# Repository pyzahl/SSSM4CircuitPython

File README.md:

# SSSM4CircuitPython
Solar Scintillation Seeing Monitor (SSSM) for CircuitPython

A renewed verion of a SSSM for CircuitPython on a ESP32-S2 or -S3-TFT.

Project based on hardware described here
https://www.blackwaterskies.co.uk/2017/06/diy-solar-scintillation-seeing-monitor-sssm/
or originally here:
https://vdocuments.mx/an-inexpensive-solar-scintillation-seeing-monitor-circuit-an-inexpensive.html

Let me copy the intro to SSSM:

A guide to building an inexpensive Solar Scintillation Seeing Monitor. The SSSM is a handy device which monitors the atmospheric seeing conditions during solar imaging. This SSSM can be built for a fraction of the cost of commercially available devices. You can use the SSSM to monitor seeing conditions through the day, or even to control your camera to capture images during the best seeing conditions.

Background:
The original design for the SSSM was published by E. J. Seykora at the Department of Physics, East Carolina University.

Read also how to integrate with Firecapture:
http://www.firecapture.de/
http://www.joachim-stehle.de/downloads/SSSMon/SSSMonPluginManual.pdf

Adapted schematics, connected to A0 and A1 for the ESP32-S2/S3-TFT replacing the originally used arduino.

This project is based on CircuitPython Version 8 (all required Libs included for reference) running on a Adafruit ESP32-S2/S3-TFT. The S3 is faster and better suited.

Anyhwo, the new S3 seams to have issues with WiFi. WiFi is not required here in USB-Serial mode compatible with the original Firecapture SSSM plugin and interface. Anyways planns are to use for MQTT for web based publishing, this works with the ESP32-S2-TFT, even not long term stable. Causes "Wifi-OFF" Progra mhold on the S3. TDB. May be next gen/version of Circuit Python fixes it. 

Currently: CircuitPython 8.0.0-beta.6

https://circuitpython.org/board/adafruit_feather_esp32s3_tft/

Adafruit ESP32-S3 TFT Feather - 4MB Flash, 2MB PSRAM, STEMMA QT:

https://www.adafruit.com/product/5483
https://github.com/adafruit/Adafruit-ESP32-S3-TFT-Feather-PCB

Pinouts:

https://learn.adafruit.com/assets/114106

Optional support for digital LUX light sensor TSL2591: Lux and Mag reading.

Read the python code.py for details ;)

1) virtual zero volt calibration (about 3.3V/2 = 0V what is apporx a reading mapped to 32768. Exact dark values can be determined in "Zero Calibration Mode". And adjusted in the code.py in the top part lines 42,43.

```
#### original build V0
Analog0InCenter   = 32603
Analog1InCenter   = 32643
```

2) Operation Modes selectable via DIP Switch in my buid on pins A2,A3,A4,A5 -- open or closed to GND.

Alternatively the modes may be set via code overide liek this:
```
# DIP SWITCH INFO
print ('Note: DIP ON (=GND) := False')
for pin in sorted(DipSW):
	DipSW[pin].switch_to_input(pull=Pull.UP)

# override or set DIP wo dip sw in place:
#DipSW['2'].switch_to_input(pull=Pull.DOWN)
DipSW['3'].switch_to_input(pull=Pull.DOWN)
```

DIP Switch Assignments are:
```
## Operation Modes
DipSW = {
	'1': DigitalInOut(board.A2),  ## Read/Write (DIP on := GND [==Logic False]) => recording to logfile / no recording
	'2': DigitalInOut(board.A3),  ## WiFi+MQTT Logging On/Off  *** disabled Use I2C Sensor
	'3': DigitalInOut(board.A4),  ## FireCapture prints/Full report prints to console
	'4': DigitalInOut(board.A5),  ## Zero Calib Info ON / OFF
	}

DipSWinfoClosed = { ## Logic "False" as DIP=ON is pin on GND
        '1': 'Record to Logfile',
        '2': 'WiFi+MQTT IoT Transmit',
        '3': 'FC Print',
        '4': 'Zero Offset Calibration',
        }

DipSWinfoOpen = { ## Logic "True" = OPEN/OFF
        '1': 'No Logging',
        '2': 'No Wifi+MQTT',
        '3': 'Long Status Print',
        '4': 'Normal Operation',
        }
```

When hooked up to USB Serial (ttyACM0,..) terminal (CuteCom, screen,... or similar):

```
--- STARTUP ---

Auto-reload is on. Simply save files over USB to run them or enter REPL to disable.
code.py output:
<0x1b>]0;<0xf0><0x9f><0x90><0x8d>Wi-Fi: off | code.py | 8.0.0-beta.6<0x1b>\<0x1b>]0;<0xf0><0x9f><0x90><0x8d>Wi-Fi: No IP | code.py | 8.0.0-beta.6<0x1b>\Note: DIP ON (=GND) := False
Dip SW 1 Off: No Logging
Dip SW 2 Off: No Wifi+MQTT
Dip SW 3 On:  FC Mode
Dip SW 4 Off: Normal Operation
I2C addresses found: ['0xb']
Battery Percent: 100.00 %
Battery Voltage: 4.18 V
WiFi OFF, no NTP auto time set.
System Start Timestamp: 2000 01 01  01:15:23
MQTT disabled.
Checking for LUX sensor TSL2591
No I2C device at address: 0x29
... none
***
Zero Cal Init: [I, R, U0, U1]    20   19 1662 1662 mV  403.4  369.5 33007.3 33012.9
Zero Offset Calibration Warning! Please check dark.
***
Actual Center:  33007  33013
Actual Center:  33007  32998
Actual Center:  33008  33011
Actual Center:  33004  33008
***
I2C addresses found: ['0xb']
A0: 0.02
A1: 9.99
D0: 10.00
C2: 0.40
A0: 0.02
A1: 9.99
D0: 10.00
C2: 0.81
A0: 0.02
A1: 9.99
D0: 10.00
C2: 1.22
A0: 0.02
A1: 9.99
```

```
Wi-Fi: off | code.py | 8.0.0-beta.6
Wi-Fi: No IP | code.py | 8.0.0-beta.6
Note: DIP ON (=GND) := False
Dip SW 1 True No Logfile
Dip SW 2 False MQTT IoT Transmit
Dip SW 3 False FC Print
Dip SW 4 False WiFi
Battery Percent: 57.40 %
Battery Voltage: 3.87 V
Connecting WiFi...
Connecting to 31A138_5G
try: NTP clock sync...
try: Sync system time to NTP...
Start Timestamp: 2023 01 13  06:51:27
MQTT Client Configuration:
MQTT: Attempting to connect to 192.168.0.20::1883
Connected to MQTT Broker!
Flags: 0
 RC: 0
Checking for LUX sensor TSL2591
No I2C device at address: 0x29
... none
A0: 1.01
A1: 0.27
C2: 0.03
MQTT publishing...
A0: 1.01
A1: 0.25
C2: 0.05
MQTT publishing...
A0: 1.01
A1: 0.26
C2: 0.08
MQTT publishing...
A0: 1.01
A1: 0.27
C2: 0.10
MQTT publishing...
A0: 1.01
A1: 0.27
C2: 0.13
MQTT publishing...
A0: 1.01
A1: 0.27
C2: 0.16
```

```
Note: DIP ON (=GND) := False
Dip SW 1 Off: No Logging
Dip SW 2 On:  WiFi+MQTT IoT Transmit
Dip SW 3 On:  FC Print
Dip SW 4 Off: Normal Operation
I2C addresses found: ['0xb']
Battery Percent: 1.40 %
Battery Voltage: 3.95 V
Connecting WiFi...
Connecting to 31A138_5G
Connected to 31A138_5G!
try: NTP clock sync...
try: Sync system time to NTP...
Start Timestamp: 2023 01 31  08:54:03
MQTT Client Configuration:
MQTT: Attempting to connect to 192.168.0.20::1883
Connected to MQTT Broker!
Flags: 0
 RC: 0
Checking for LUX sensor TSL2591
No I2C device at address: 0x29
... none
***
Zero Cal Init: [I, R, U0, U1]  -1602 -1604   40   39 mV -31814.8 -31859.6  788.2  770.0
Zero Offset Calibration Warning! Please check dark.
***
Actual Center:    788    770

*** WiFi issue here...
Wi-Fi: off | Done | 8.0.0-beta.6
Auto-reload is off.
```

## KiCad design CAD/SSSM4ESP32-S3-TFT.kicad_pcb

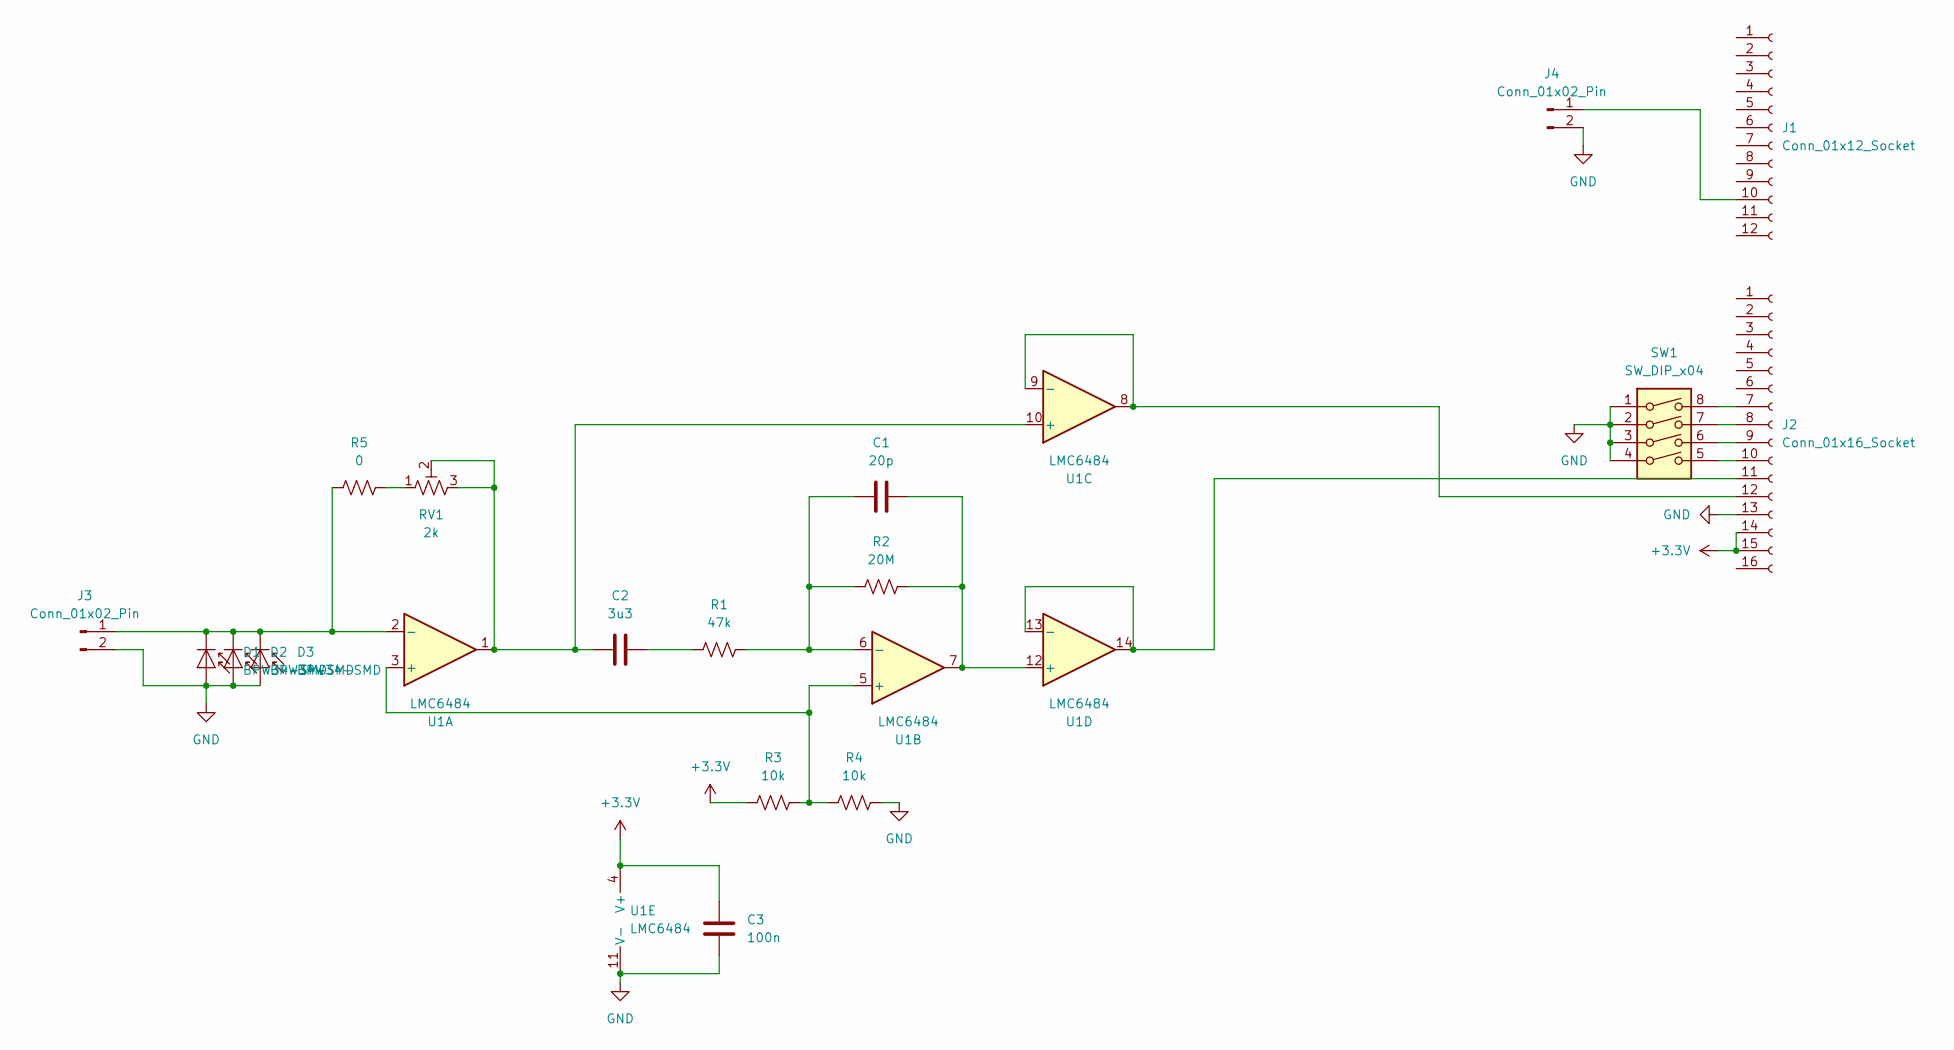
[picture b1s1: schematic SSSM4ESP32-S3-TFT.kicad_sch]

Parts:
C1: 20p; C_1210_3225Metric
C2: 3u3; C_1210_3225Metric
C3: 100n; C_1210_3225Metric
D1, D2, D3: BPW34-SMD; Osram_BPW34S-SMD
J1: Conn_01x12_Socket
J2: Conn_01x16_Socket
J3, J4: Conn_01x02_Pin; JST_PH_B2B-PH-K_1x02_P2.00mm_Vertical
R1: 47k; R_1206_3216Metric
R2: 20M; R_1206_3216Metric
R3, R4: 10k; R_1206_3216Metric
R5: 0; R_1206_3216Metric
RV1: 2k; Potentiometer_Bourns_3224X_Vertical
SW1: SW_DIP_x04; SW_DIP_SPSTx04_Slide_6.7x11.72mm_W8.61mm_P2.54mm_LowProfile
U1: LMC6484; SOIC-14_3.9x8.7mm_P1.27mm

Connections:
+3.3V: C3.2, J2.14, J2.15, R3.1, U1.4 (V+)
GND: C3.1, D1.2 (A), D2.2 (A), D3.2 (A), J2.13, J3.2, J4.2, R4.2, SW1.1, SW1.2, SW1.3, SW1.4, U1.11 (V-)
unnamed: C2.2, R1.1
unnamed: D1.1 (K), D2.1 (K), D3.1 (K), J3.1, R5.1, U1.2 (-)
unnamed: J1.10, J4.1
unnamed: J2.7, SW1.8
unnamed: J2.8, SW1.7
unnamed: J2.9, SW1.6
unnamed: J2.10, SW1.5
unnamed: J2.11, U1.13 (-), U1.14
unnamed: J2.12, U1.8, U1.9 (-)
unnamed: R5.2, RV1.1
unnamed: R3.2, R4.1, U1.3 (+), U1.5 (+)
unnamed: C1.1, R1.2, R2.1, U1.6 (-)
unnamed: C2.1, RV1.2, RV1.3, U1.1, U1.10 (+)
unnamed: C1.2, R2.2, U1.7, U1.12 (+)

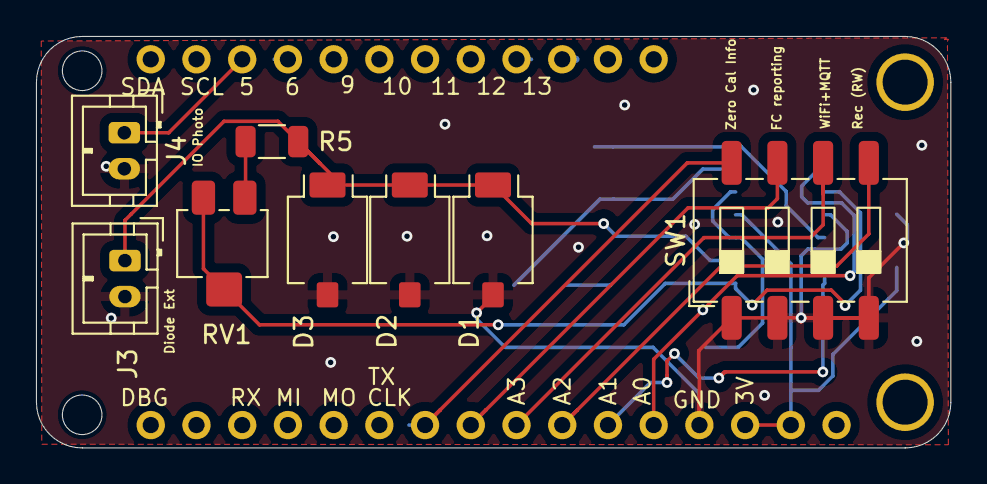
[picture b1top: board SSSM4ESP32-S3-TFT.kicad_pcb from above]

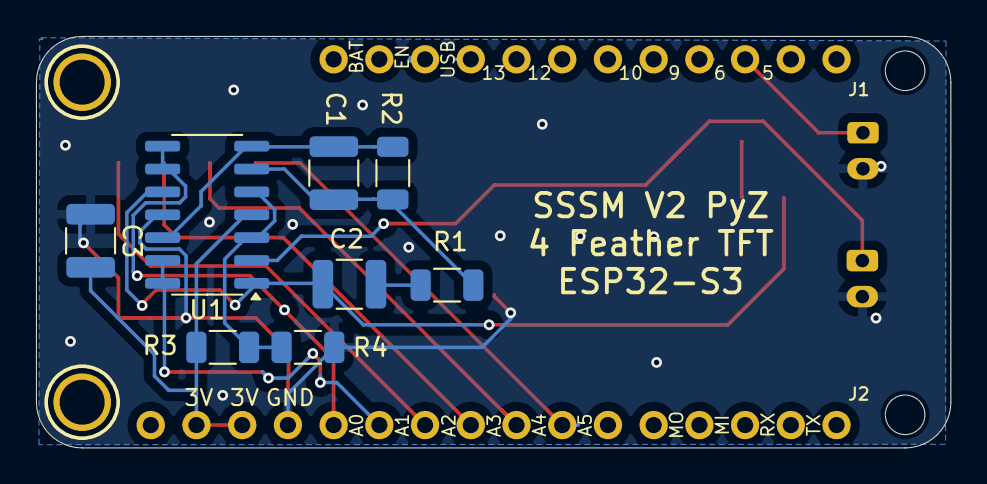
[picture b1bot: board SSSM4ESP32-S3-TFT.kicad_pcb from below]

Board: 2 copper layers, 50.8 x 22.9 mm, 22 parts (12 on the bottom side), 16 nets.

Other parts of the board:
U$31, U$32: MOUNTINGHOLE2.5; MOUNTINGHOLE_2.5_PLATED
UNK_HOLE_0: dummyfp0
UNK_HOLE_1: dummyfp1

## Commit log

2023-01-13 Circuit Python 8 Libs required
2023-01-15 Add files via upload
    Cleanup and new revisions uploaded
2023-01-15 Add files via upload
    Added and updated
2023-01-15 Add files via upload
    updates
2023-02-17 added clamp
    added clamp 154.4mm
2023-02-18 SSSM monitor log file plot tool
2023-02-18 Add files via upload
    update
2023-02-18 Add files via upload
    add cmd arg for log file
2023-02-18 Add files via upload
    update display: use median seeing
2023-02-25 Add files via upload
    With Bracket for 155mm tube
2023-03-04 Rename file
